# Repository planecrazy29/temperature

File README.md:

This is a simple temperature controller using an arduino bootloaded atmega328p, a 16x2 LCD display, and a ds18b20 temperature sensor.  Comments, questions or concerns can be emailed to planecrazy29@gmail.com

This is my first attempt at a project of this type including figuring out github, so please let me know if I do something wrong or you can help me make it better.  Thanks.

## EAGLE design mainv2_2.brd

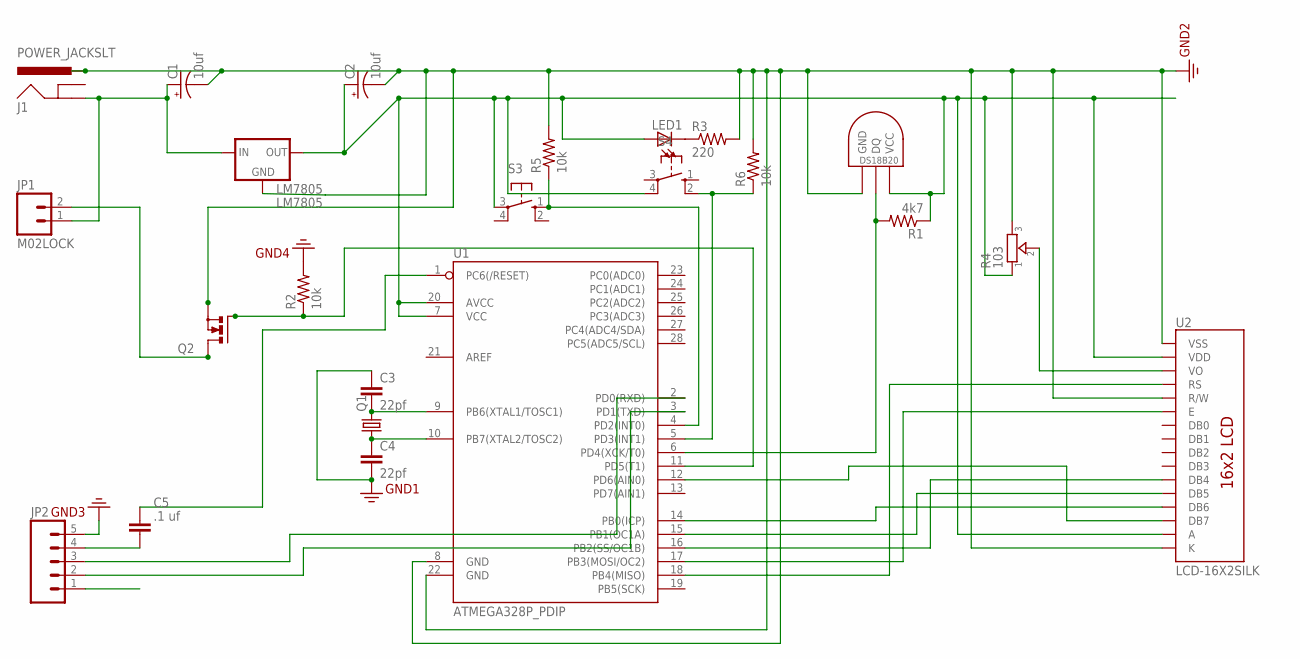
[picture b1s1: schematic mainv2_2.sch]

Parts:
C1, C2: 10uf; CPOL-RADIAL-10UF-25V
C3, C4: 22pf; CAP-PTH-SMALL2
C5: .1 uf; C0.1PTH
J1: POWER_JACKSLT; POWER_JACK_SLOT
JP1: M02LOCK; 1X02_LOCK
JP2: M05PTH; 1X05
LED1: LED3MM
LM7805: LM7805; TO220-IGO
Q1: CRYSTALHC49S; HC49/S
Q2: PMOSFET_NTO220BV; TO220BV
R1: 4k7; AXIAL-0.3
R2, R5, R6: 10k; AXIAL-0.3
R3: 220; AXIAL-0.3
R4: 103; TRIMMER_3306F
S3, S4: 10-XX; B3F-10XX
U1: ATMEGA328P_PDIP; DIL28-3
U2: LCD-16X2SILK; LCD-16X2
U$1: DS1820TO92; DS1820

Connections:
+12: C1.1 (+), J1.GND@2 (GND), JP1.1, LM7805.IN
GND: C1.2 (-), C2.2 (-), C3.1, C4.2, J1.PWR, JP2.5, LM7805.GND, Q2.S, R2.P$2 (2), R3.P$2 (2), R4.3, R5.P$2 (2), R6.P$2 (2), U1.8 (GND), U1.22 (GND), U2.1 (VSS), U2.5 (R/W), U2.16 (K), U$1.GND
unnamed: C5.2, JP2.4
unnamed: C5.1, U1.1 (PC6(/RESET))
unnamed: U1.16 (PB2(SS/OC1B)), U2.11 (DB4)
unnamed: C3.2, Q1.2, U1.9 (PB6(XTAL1/TOSC1))
unnamed: C4.1, Q1.1, U1.10 (PB7(XTAL2/TOSC2))
unnamed: U1.15 (PB1(OC1A)), U2.12 (DB5)
unnamed: U1.14 (PB0(ICP)), U2.13 (DB6)
unnamed: U1.18 (PB4(MISO)), U2.4 (RS)
unnamed: U1.17 (PB3(MOSI/OC2)), U2.6 (E)
unnamed: R4.2, U2.3 (VO)
unnamed: U1.12 (PD6(AIN0)), U2.14 (DB7)
unnamed: Q2.G, R2.P$1 (1), U1.11 (PD5(T1))
unnamed: R5.P$1 (1), S3.1 (S), U1.4 (PD2(INT0))
unnamed: JP1.2, Q2.D
unnamed: LED1.K (C), R3.P$1 (1)
unnamed: R6.P$1 (1), S4.2 (S1), U1.5 (PD3(INT1))
unnamed: JP2.2, U1.3 (PD1(TXD))
unnamed: JP2.3, U1.2 (PD0(RXD))
TEMP: R1.P$2 (2), U1.6 (PD4(XCK/T0)), U$1.DQ
VCC: C2.1 (+), JP2.1, LED1.A, LM7805.OUT, R1.P$1 (1), R4.1, S3.3, S4.4 (P1), U1.7 (VCC), U1.20 (AVCC), U2.2 (VDD), U2.15 (A), U$1.VDD (VCC)

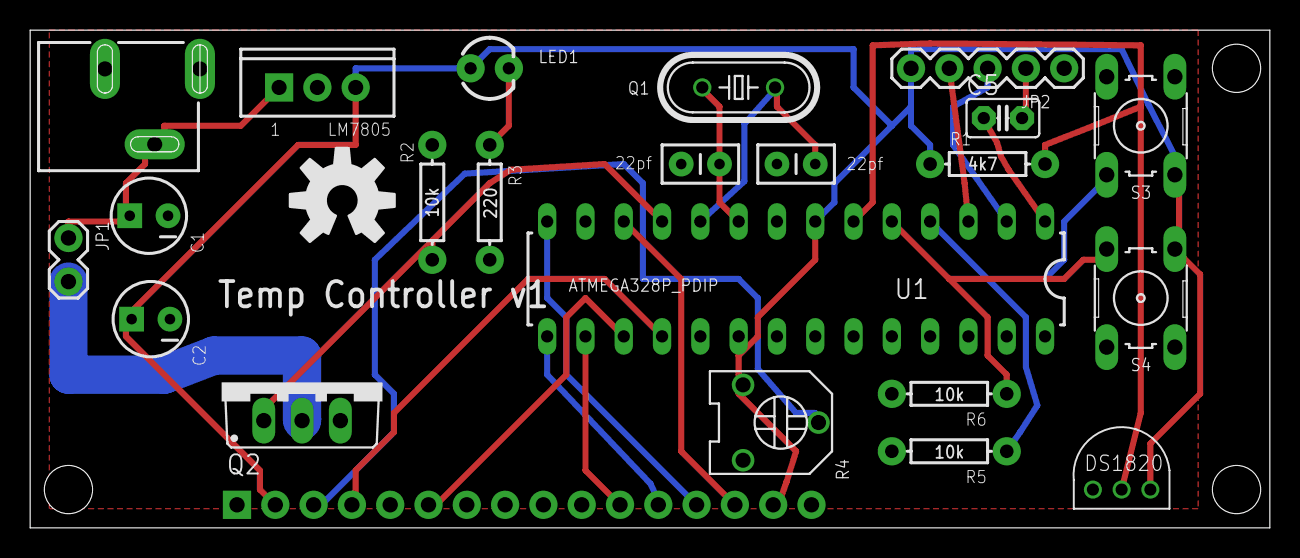
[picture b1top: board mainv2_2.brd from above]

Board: 2 copper layers, 82.2 x 33.0 mm, 24 parts (0 on the bottom side), 22 nets.

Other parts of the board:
U$3: OSHW-LOGO-L

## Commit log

2014-04-05 first files
2014-04-05 add README
2014-04-05 project files added
    Arduino code, eagle schematic and boar files
2014-04-06 add to do list

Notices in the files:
parts and their libraries:
SparkFun-DigitalIC: Licensing: Creative Commons ShareAlike 4.0 International - https://creativecommons.org/licenses/by-sa/4.0
